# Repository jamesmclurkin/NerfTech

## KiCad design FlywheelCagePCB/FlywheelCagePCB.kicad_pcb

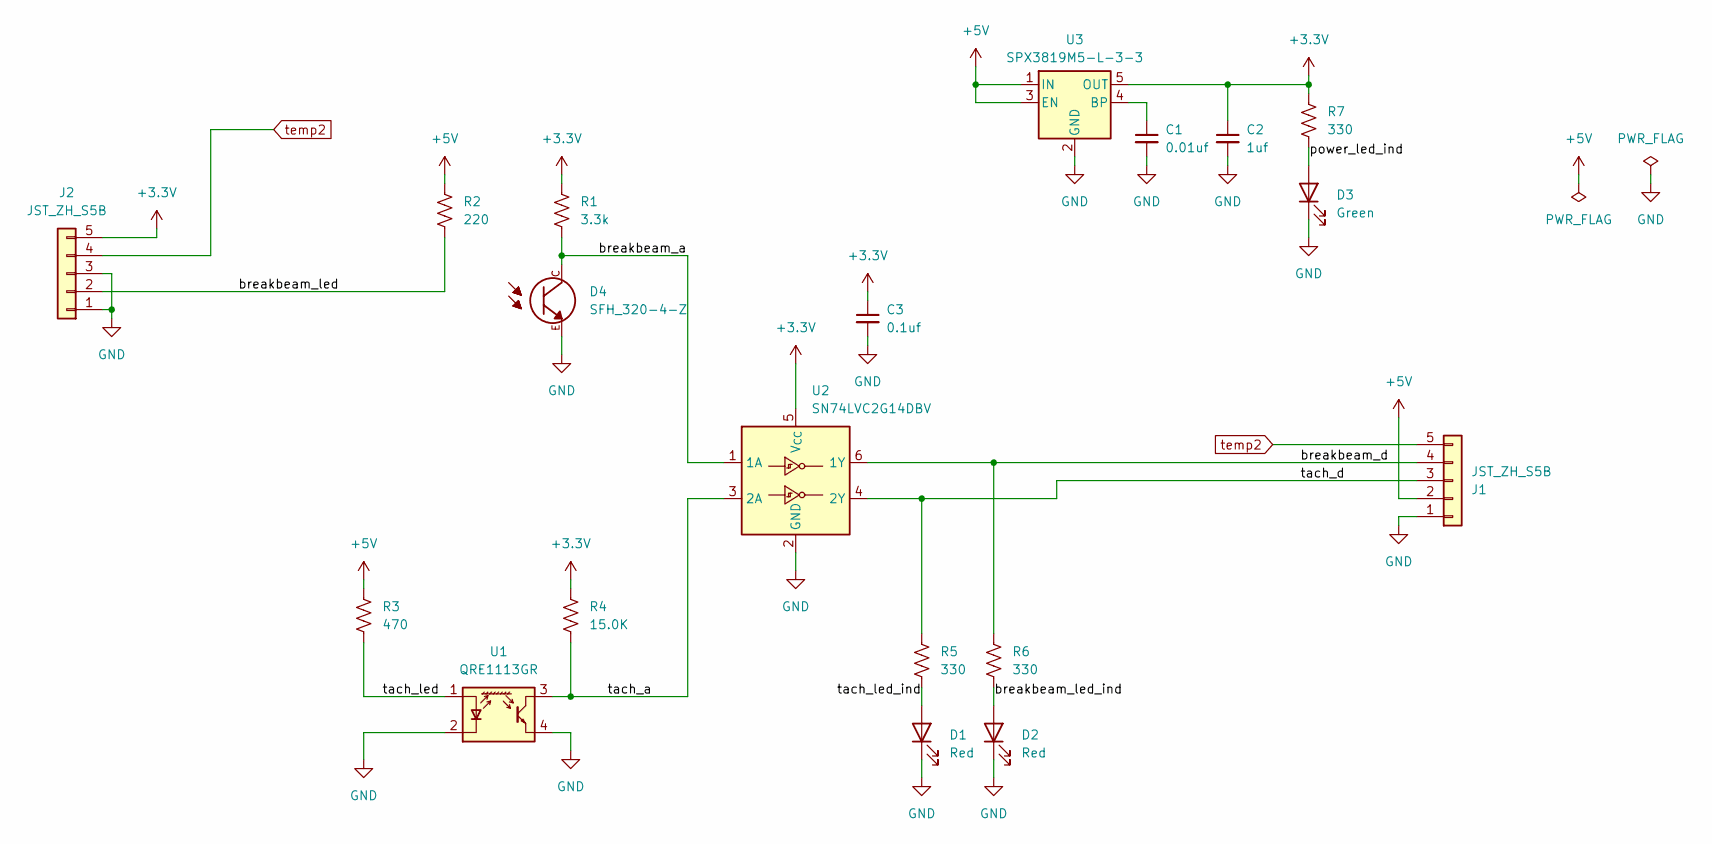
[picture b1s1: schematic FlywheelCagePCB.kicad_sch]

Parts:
C1: 0.01uf; C_0603_1608Metric; PartNumber 399-C0603C103K5RACTUCT-ND
C2: 1uf; C_0603_1608Metric; PartNumber 399-C0603C105K3RACTUCT-ND
C3: 0.1uf; C_0603_1608Metric; PartNumber 399-C0603C104M5RACTUCT-ND
D1, D2: Red; LED_0603_1608Metric; PartNumber 475-KSEELP41.22-P1R2-58-A8J8-020-R18CT-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
D3: Green; LED_0603_1608Metric; PartNumber 475-KGEELP41.22-PHRH-35-A8J8-20-R18CT-ND
D4: SFH_320-4-Z; PHODET_SFH_320-4-Z; PARTREV 1.7
J1, J2: JST_ZH_S5B; JST_ZH_B5B-ZR_1x05_P1.50mm_Horizontal; PartNumber 455-S5B-ZR-ND
R1: 3.3k; R_0603_1608Metric; PartNumber 311-3.30KHRCT-ND
R2: 220; R_0603_1608Metric; PartNumber 311-220HRCT-ND
R3: 470; R_0603_1608Metric; PartNumber 311-470HRCT-ND
R4: 15.0K; R_0603_1608Metric; PartNumber 311-15.0KHRCT-ND
R5, R6, R7: 330; R_0603_1608Metric; PartNumber 311-330HRCT-ND
U1: QRE1113GR; OnSemi_CASE100CY; PartNumber QRE1113GRCT-ND
U2: SN74LVC2G14DBV; SOT-23-6; PartNumber 1727-6088-1-ND
U3: SPX3819M5-L-3-3; SOT-23-5; PartNumber 1016-1873-1-ND

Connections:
+3.3V: C2.1, C3.1, J2.5, R1.1, R4.1, R7.1, U2.5 (V_{CC}), U3.5 (OUT)
+5V: J1.2, R2.1, R3.1, U3.1 (IN), U3.3 (EN)
/breakbeam_a: D4.C, R1.2, U2.1 (1A)
/breakbeam_d: J1.4, R6.1, U2.6 (1Y)
/breakbeam_led: J2.2, R2.2
/breakbeam_led_ind: D2.2 (A), R6.2
/power_led_ind: D3.2 (A), R7.2
/tach_a: R4.2, U1.3, U2.3 (2A)
/tach_d: J1.3, R5.1, U2.4 (2Y)
/tach_led: R3.2, U1.1 (A)
/tach_led_ind: D1.2 (A), R5.2
GND: C1.2, C2.2, C3.2, D1.1 (K), D2.1 (K), D3.1 (K), D4.E, J1.1, J2.1, J2.3, U1.2 (K), U1.4, U2.2 (GND), U3.2 (GND)
unnamed: C1.1, U3.4 (BP)
temp2: J1.5, J2.4

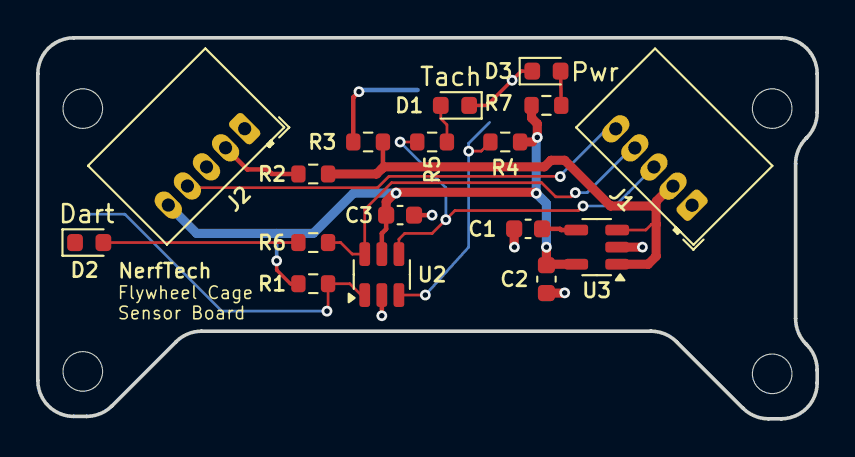
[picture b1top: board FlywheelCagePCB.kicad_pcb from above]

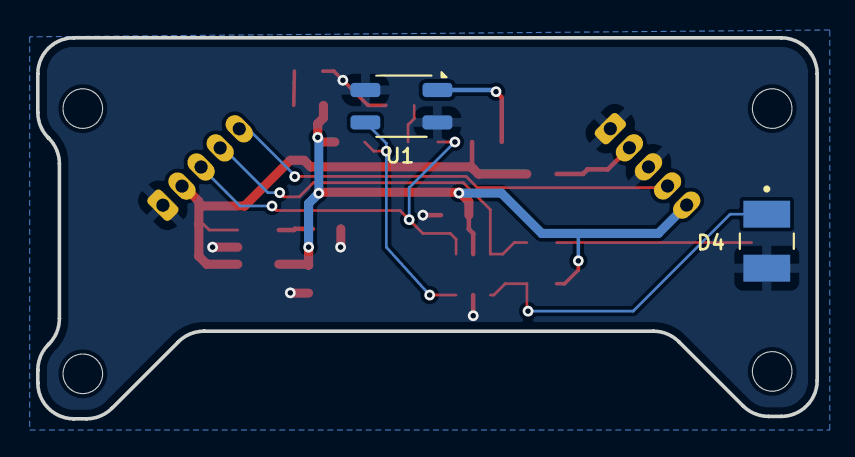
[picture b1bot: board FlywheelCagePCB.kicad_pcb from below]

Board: 2 copper layers, 43.3 x 21.2 mm, 19 parts (2 on the bottom side), 14 nets.

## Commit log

2016-09-25 Initial commit of NerfTech code for RapidStrike, Stryfe, and MegaMortar
2016-09-29 STarted adding port expander code to the stryfe to read mag sensors
2016-09-29 moved gpio code from mortar to stryfe code
2016-10-03 Started config options
2016-10-03 Added some example config structs
2016-10-03 Added pressure sensor reading to mega mortar Displayed in LED for calibration
2016-10-03 Tested mag GPIO pins
2016-10-09 Added AlphaTrooper project
2016-10-18 calibrated megamortar pressure gauge Added raw maggpio print for alpha trooper
2016-10-28 Edited mag sensor files for final orientation of sensor boards slowed down rapid strike full auto rate
2016-10-28 Added ALphatrooper HUD port expander code
2017-02-19 Added I2C debugging for rapidstrke reorganized stryfe and rapidstrike code to be similar
2017-02-19 Added screen disable flag
2017-02-20 minor project tweaks
2017-03-05 started on port to pro micro board
2017-03-05 Added beter pin disgram
2017-03-12 Added more docs for various chips and baords
2017-03-18 Added conditional compilaion for both GPIO port expanders
2017-03-19 Added more datasheets
2017-03-25 Final commit before moving to CodeBlox
2017-03-26 Initial commit of codeblox nerfcomp project
2017-04-01 Moved variables to Flash progmem moved images and fonts to lib directory
2017-04-01 Added libraries dir added merfcomp to librries dir
2017-04-01 Added Codeblox rapidstrike project
2017-04-01 removed rapidstrike eclipse project
2017-04-06 Started config screen
2017-04-06 solved display oddness with a global variable
2017-04-08 Finished scrolling for config screen
2017-04-09 Config Parameter editor working!
2017-04-12 State before removing temp variables
2017-04-15 remove config screen temp RAM variables
2017-04-20 Added menu, did not test
2017-04-21 Menu worked pretty much on the first try. wow
2017-04-23 Added missing header file
2017-04-24 Fixed config param init and progrmming removed feed jam FSM
2017-09-09 Added memory debugging sheet
2017-09-15 Added cscope zip file
2017-09-15 Added cscope binary to zip file
2017-09-15 Added readme to csope zip file added setup.txt to project dir
2017-10-01 Tweaked jam time and typo
2017-10-07 Broke RapidStrike code into libraries Added Display library
2017-10-08 Moved config variables back to main file, made UI for eadling them them.
2017-10-09 Addad gpio lib, reorganized functions
2017-10-10 commit before stryfe refactor
2017-10-16 Rapid Strike Complies and seems to work. Started refactoring Stryfe code
2017-11-12 Started Stryfe Port
2017-11-27 Reorg to clean up main ino file moved dart sensing and heartbeat functions into nerfcomp and nerfcompio
2017-12-02 Moved FSM into self-contained function abstrated display control
2018-04-01 minor display mods
2025-04-06 NerfTech 2.0. Initial commit for solenoid stryfe blaster. Big library update and directory reorg
2025-04-15 Final commit for solenoid, copied to worker auto
2025-04-16 started analog write for plunger - need to test output
2025-04-16 final solenoid commit. dissappointing performance
2025-04-18 Giant progress on plunger FSM
2025-04-18 re-enabled flywheel
2025-04-22 initial commit of Vulcan code. Might be working , but ESC is acting odd
2025-04-23 nice vulcan auto fire control FSM
2025-04-24 tuning parameters for testing first darts
2025-04-25 RFID Tags working and parsing
2025-05-16 Added flywheel sensor board PCB design
2025-05-17 added resistors to flywheel pcb
2025-05-17 added KiCad library tables
2025-05-19 moved PCB components a bit
2025-05-19 Added 3d models for JST ZH connectors. Made 3d Step output
2025-05-19 Added caps. Need to get part numbers
2025-05-19 placement complete. started routing
2025-05-19 Tape out on V0.1
2025-05-19 BOM scrubb
2025-05-20 SLowed down Atryfe worker auto to make it a bit more reliable in stopping
2025-05-21 increased Vulcan belt speed a bit for testing
2025-05-21 edited PCB colors. Clanged origin point for 3D output
2025-05-23 fixed motor controller for Stryfe. Removed .vscode directories
2025-05-23 Fixed motor plunger driver for stryfe
2025-05-23 Removed the slow down states from the FSM. Trigger is as snappy as it can be
2025-05-28 BOM. FIrst PCB build
2025-05-28 Tach Test
2025-05-28 added zero logic ro tach
2025-05-29 Reasonable FPS measurements from the break beam
2025-05-30 Added dotstar LED to GPIO Test
2025-06-01 testing drvmotor driver. wierd problems with coast()
2025-06-01 changed all motor outputs to PWM outputs
2025-06-03 put lowside driver back into vulcan. move tach, led, breakbeam code to vulcan
2025-06-04 gated plunger firing to RPM! CHanged color order in adafruit dotstar library
2025-06-04 git directory reorginazation
2025-06-04 Directory reorganization
2025-06-04 edited pcb paths in git ignore
2025-06-04 stopped tracking ignored files
2025-06-04 started refactor of Tachometer lib
2025-06-05 moved nerftech libs out of src directory
2025-06-05 moved nerftech libs out of src drectory
2025-06-05 Tach Library working! And in the right location
2025-06-05 Made Tach and breakbeam library. Tach library tested fine
2025-06-05 installed todo manager
2025-06-07 abstracted all four motor drivers. Need to build a test rig and test
2025-06-09 Started porting display code
2025-06-09 Moved HUD Code over to new library with temporary variables
2025-06-09 Splash screen on display!
2025-06-10 Got old HUD up and working
2025-06-10 HUD display up and working. Lots of fun with fonts
2025-06-11 Started on display buttons code
2025-06-15 DIsplay integrated into Vulcan. Neat!
2025-06-15 RFID tested in actual assembled vulcan!
